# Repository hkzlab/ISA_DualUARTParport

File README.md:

# Dual UART + Parallel port ISA adapter

## Introduction

This board adds a parallel port and two serial (RS232) ports to computers with a free ISA slot.

The schematics of this board is heavily inspired by the parallel port schematics found in the IBM 5150 Technical Reference, with just a few
changes (IRQ level triggering and configurable port directionality) and by Sergey's floppy/serial controller.

Both serial ports and the parallel port addressing/IRQs are configurable.

### Disclaimer

I take NO responsibility for what happens if you decide to build and use this card. Your computer might crash, catch fire or be destroyed in other nasty ways.
Also, as this card is mostly based on the work of others, You're encourauged to take what you deem fit from this, and use it in your projects!

## Configuration

### Parallel port

#### Addressing

- 0x278: Leave JP1 open
- 0x378: Close JP1

#### IRQ

Parallel port interrupt number can be selected by placing a single vertical jumper on the **ParPort IRQ** block.

For example, a jumper placed on the last column of that block, will set the IRQ for the parallel port to number 7.

#### Directionality

The parallel port can be configured as an old style 4bit, monodirectional, parallel port by jumpering pins 2-3 of JP2.
PS/2 style bidirectional port can be configured by jumpering pins 1-2.

### Serial ports

IRQ and addressing of serial ports can be configured by properly jumpering the 3x8 jumper block at the center of the board.

IRQ selection is performed by the first 4 rows of the block: placing an horizontal jumper between columns 1-2 will select IRQ for the first serial port, between columns 2-3 will select
the IRQ for the second serial port.

The same principle applies for the IO address, selected by the last 4 rows of the block: jumpers between column 1-2 will select an address for port 1, and between column 2-3 for port 2.

#### Example

To select IO at 0x3F8 and IRQ4 for port 1, connect a jumper on 2nd row, first two columns, and another jumper on 8th row, column 1-2

## Bill of Materials

All ICs are in DIP package.

- 4x ~2.2k 1/4W resistors (**optional**, R1-R4). **These resistors will be on the TTL RX/TX lines**. To avoid loading them too much, use high-brightness leds and the highest resistor value you can use that still gives enough brightness!
- 4x 3mm LEDs (2x for UART RX indicators, 2x for TX) (**optional**)
- 1x 1.8432Mhz oscillator. DIP14 or DIP8
- 1x 8x4.7k bussed resistor array (9 pin)
- 1x 10x1.5k bussed resistor array (11 pin) (**optional**)
- 1x 10x LED bar, DIP20 (**optional**, socket this!)
- 8x 2.2nF / 25V ceramic capacitors, 5mm pitch
- 18x 100nF / 50v ceramic capacitors, 5mm pitch
- 4x 10uF / 50v electrolytic caps
- 2x 16C550 UARTs (16C450/16C650/16C750 should work, but are untested) in DIP40 format
- 2x 74HCT/LS138
- 2x 75C185
- 1x 74LS245
- 1x 74LS240
- 1x 74LS374
- 1x 74LS244
- 1x 74LS02
- 1x 74LS155
- 1x 74LS05
- 1x 74LS174
- 1x 74LS30
- 1x 74LS125
- 1x 74LS86
- 1x 2x13 pin header, 2.54mm
- 1x 2x4 pin header, 2.54mm
- 1x 2x8 pin header, 2.54mm
- 1x 1x8 pin header, 2.54mm
- 1x 1x2 pin header, 2.54mm
- 1x 1x3 pin header, 2.54mm
- 1x DB9 male, right angle, PCB mount (http://www.mouser.com/search/refine.aspx?Keyword=806-K22X-E9P-NJ15-99)
- 1x ISA card bracket - Keystone 9200-1 (http://www.mouser.com/ProductDetail/Keystone-Electronics/9200-1/?qs=sGAEpiMZZMsQtlBhqKq43VLJ3wppkop5) 

## Building notes

I **strongly advise AGAINST** soldering the LED bar for the parallel port: **socket it!** It is useful for debugging or to get some blinkenlights, but it loads the data pins, and some devices connected to the port might not like it. Socketing it will allow for a quick removal in case it becomes necessary.

RN2 depends on how bright you wish the LED bar to be, and how much load you want to put on the parallel port data pins. I usually fit an 1.5k resistor array.

## Credits

Thanks to [Sergey](http://www.malinov.com/Home/sergeys-projects) for all his projects!

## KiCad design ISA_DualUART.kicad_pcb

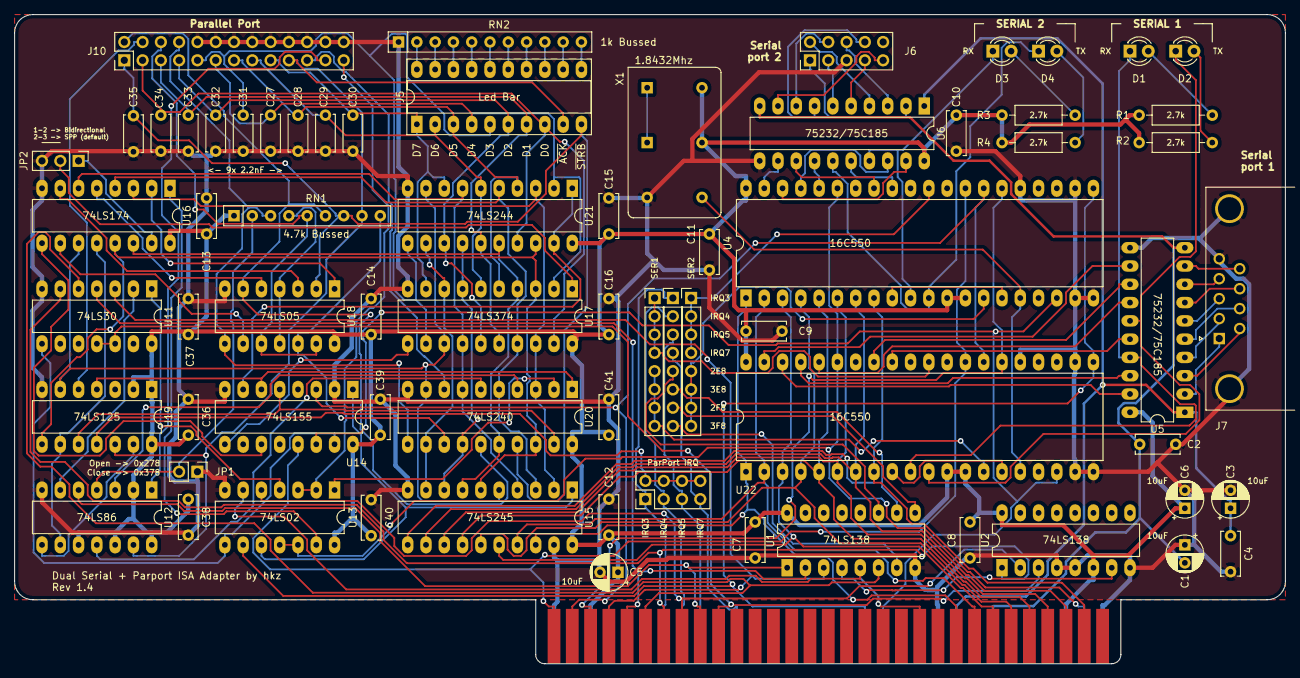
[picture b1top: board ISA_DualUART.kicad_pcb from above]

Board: 2 copper layers, 176.5 x 90.2 mm, 70 parts (0 on the bottom side), 138 nets.

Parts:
C1, C3, C5, C6: 10uF; CP_Radial_D5.0mm_P2.50mm
C2, C4, C7, C8, C9, C10, C11, C12, C13, C14, C15, C16, C36, C37, C38, C39, C40, C41: 100nF; C_Disc_D6.0mm_W2.5mm_P5.00mm
C27, C28, C29, C30, C31, C32, C33, C34, C35: 2.2nF; C_Disc_D5.0mm_W2.5mm_P5.00mm
D1: LED RX1; LED_D3.0mm
D2: LED TX1; LED_D3.0mm
D3: LED RX2; LED_D3.0mm
D4: LED TX2; LED_D3.0mm
J1: ISA BUS; Conn_Edge_PCB_ISA8
J2: ADDR_IRQ; PinHeader_1x08_P2.54mm_Vertical
J3: UART1_SEL; PinHeader_1x08_P2.54mm_Vertical
J4: UART2_SEL; PinHeader_1x08_P2.54mm_Vertical
J5: Parallel Port LEDs; DIP-20_W7.62mm_Socket_LongPads
J6: Serial 2 IDC; PinHeader_2x05_P2.54mm_Vertical
J7: Serial 1 DB9; DSUB-9_Male_Horizontal_P2.77x2.84mm_EdgePinOffset7.70mm_Hou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
J9: Parport IRQ Select; PinHeader_2x04_P2.54mm_Vertical
J10: Parallel Port; PinHeader_2x13_P2.54mm_Vertical
JP1: Address selection; PinHeader_1x02_P2.54mm_Vertical
JP2: Parport type; PinHeader_1x03_P2.54mm_Vertical
R1, R2, R3, R4: 2.7k; R_Axial_DIN0207_L6.3mm_D2.5mm_P10.16mm_Horizontal
RN1: 4.7k; R_Array_SIP9
RN2: 1k; R_Array_SIP11
U1, U2: 74LS138; DIP-16_W7.62mm_LongPads
U4, U22: 16550; DIP-40_W15.24mm_LongPads
U5, U6: GD75232N; DIP-20_W7.62mm_LongPads
U11: 74LS30; DIP-14_W7.62mm_LongPads
U12: 74LS86; DIP-14_W7.62mm_LongPads
U13: 74LS02; DIP-14_W7.62mm_LongPads
U14: 74LS155; DIP-16_W7.62mm_LongPads
U15: 74LS245; DIP-20_W7.62mm_LongPads
U16: 74LS174; DIP-16_W7.62mm_LongPads
U17: 74LS374; DIP-20_W7.62mm_LongPads
U18: 74LS05; DIP-14_W7.62mm_LongPads
U19: 74LS125; DIP-14_W7.62mm_LongPads
U20: 74LS240; DIP-20_W7.62mm_LongPads
U21: 74LS244; DIP-20_W7.62mm_LongPads
X1: 1.8432Mhz; Oscillator_DIP-14-8

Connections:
+12V: C3.1, C4.1, J1.9, U5.1, U6.1
-12V: C1.2, C2.2, J1.7, U5.10, U6.10
/0x2E8: J2.5, U1.11
/0x2F8: J2.7, U1.9
/0x3E8: J2.6, U1.10
/0x3F8: J2.8, U1.7
/A0: J1.62, U4.28, U14.13, U22.28
/A1: J1.61, U4.27, U14.3, U22.27
/A2: J1.60, U4.26, U22.26
/A3: J1.59, U1.3, U11.3
/A4: J1.58, U1.2, U11.4
/A5: J1.57, U1.6, U11.5
/A6: J1.56, U2.1, U11.6
/A7: J1.55, U2.2, U13.5
/A8: J1.54, U1.1, U12.5
/A9: J1.53, U2.3, U11.11, U11.12
/AEN: J1.42, U1.5, U13.6
/D0: J1.40, U4.1, U15.18, U22.1
/D1: J1.39, U4.2, U15.17, U22.2
/D2: J1.38, U4.3, U15.16, U22.3
/D3: J1.37, U4.4, U15.15, U22.4
/D4: J1.36, U4.5, U15.14, U22.5
/D5: J1.35, U4.6, U15.13, U22.6
/D6: J1.34, U4.7, U15.12, U22.7
/D7: J1.33, U4.8, U15.11, U22.8
/IRQ3: J1.25, J2.1, J9.1
/IRQ4: J1.24, J2.2, J9.3
/IRQ5: J1.23, J2.3, J9.5
/IRQ7: J1.21, J2.4, J9.7
/PARPORT_BD0: U15.2, U16.3, U17.18, U20.3, U21.3
/PARPORT_BD1: U15.3, U16.4, U17.17, U20.5, U21.5
/PARPORT_BD2: U15.4, U16.6, U17.14, U20.7, U21.7
/PARPORT_BD3: U15.5, U16.11, U17.13, U19.6, U20.9, U21.9
/PARPORT_BD4: U15.6, U16.13, U17.3, U19.8, U20.18, U21.18
/PARPORT_BD5: U15.7, U16.14, U17.4, U20.16, U21.16
/PARPORT_BD6: U15.8, U17.7, U20.14, U21.14
/PARPORT_BD7: U15.9, U17.8, U20.12, U21.12
/PARPORT_BUSY: J10.21, U20.8
/PARPORT_DATA0: C34.1, J5.8, J10.3, U17.19, U21.17
/PARPORT_DATA1: C33.1, J5.7, J10.5, U17.16, U21.15
/PARPORT_DATA2: C32.1, J5.6, J10.7, U17.15, U21.13
/PARPORT_DATA3: C31.1, J5.5, J10.9, U17.12, U21.11
/PARPORT_DATA4: C27.1, J5.4, J10.11, U17.2, U21.2
/PARPORT_DATA5: C28.1, J5.3, J10.13, U17.5, U21.4
/PARPORT_DATA6: C29.1, J5.2, J10.15, U17.6, U21.6
/PARPORT_DATA7: C30.1, J5.1, J10.17, U17.9, U21.8
/PARPORT_DIR: JP2.1, U16.15
/PARPORT_IRQ: U12.11, U20.6
/PARPORT_IRQEN: U12.9, U16.12, U19.9
/PARPORT_PE: J10.23, U12.1
/PARPORT_R: U13.10, U14.1, U15.1
/PARPORT_RPA: U14.7, U21.1, U21.19
/PARPORT_RPB: U14.6, U19.4, U20.1
/PARPORT_RPC: U14.5, U19.10, U20.19
/PARPORT_SLCT: J10.25, U13.2, U13.3
/PARPORT_WPA: U14.9, U17.11
/PARPORT_WPC: U14.11, U16.9
/RESETDRV: J1.2, U4.35, U13.11, U13.12, U22.35
/RN_1: JP1.2, RN1.2, U12.4
/RN_2: J10.8, RN1.3, U18.8, U20.11
/RN_3: RN1.4, U18.4, U18.11
/RN_4: J10.6, RN1.5, U18.10, U18.13
/RN_5: J10.2, RN1.6, U18.6, U20.15
/RN_6: C35.2, J5.10, J10.1, RN1.7, U18.2, U20.17
/RN_7: J5.9, J10.19, RN1.8, U12.13, U19.12
/RN_8: RN1.9, U18.12, U20.13
/RS232_1_CTS: J7.8, U5.7
/RS232_1_DCD: J7.1, U5.2
/RS232_1_DSR: J7.6, U5.3
/RS232_1_DTR: J7.4, U5.8
/RS232_1_RI: J7.9, U5.9
/RS232_1_RTS: J7.7, U5.5
/RS232_1_RX: J7.2, U5.4
/RS232_1_TX: J7.3, U5.6
/RS232_2_CTS: J6.8, U6.7
/RS232_2_DCD: J6.1, U6.2
/RS232_2_DSR: J6.6, U6.3
/RS232_2_DTR: J6.4, U6.8
/RS232_2_RI: J6.9, U6.9
/RS232_2_RTS: J6.7, U6.5
/RS232_2_RX: J6.2, U6.4
/RS232_2_TX: J6.3, U6.6
/SER_CLK: U4.16, U22.16, X1.8
/SIN_1: D1.1, U5.17, U22.10
/SIN_2: D3.1, U4.10, U6.17
/SOUT_1: D2.1, U5.15, U22.11
/SOUT_2: D4.1, U4.11, U6.15
/UART1_IRQ: J3.1, J3.2, J3.3, J3.4, U22.30
/UART2_IRQ: J4.1, J4.2, J4.3, J4.4, U4.30
/~CTS_1: U5.14, U22.36
/~CTS_2: U4.36, U6.14
/~DCD_1: U5.19, U22.38
/~DCD_2: U4.38, U6.19
/~DSR_1: U5.18, U22.37
/~DSR_2: U4.37, U6.18
/~DTR_1: U5.13, U22.33
/~DTR_2: U4.33, U6.13
/~IOR: J1.14, U4.21, U13.9, U22.21
/~IOW: J1.13, U4.18, U14.14, U22.18
/~PARPORT_ERROR: J10.4, U19.5
/~PARPORT_IRQEN: U12.8, U19.13
/~PARPORT_RESET: U13.13, U16.1
/~RI_1: U5.12, U22.39
/~RI_2: U4.39, U6.12
/~RTS_1: U5.16, U22.32
/~RTS_2: U4.32, U6.16
/~UART1_CS: J3.5, J3.6, J3.7, J3.8, U22.14
/~UART2_CS: J4.5, J4.6, J4.7, J4.8, U4.14
GND: C1.1, C2.1, C3.2, C4.2, C5.2, C6.2, C7.2, C8.2, C9.2, C10.2, C11.2, C12.1, C13.2, C14.2, C15.2, C16.2, C27.2, C28.2, C29.2, C30.2, C31.2, C32.2, C33.2, C34.2, C35.1, C36.2, C37.2, C38.2, C39.2, C40.2, C41.2, J1.1, J1.10, J1.31, J6.5, J7.0, J7.5, J10.10, J10.12, J10.14, J10.16, J10.18, J10.20, J10.22, J10.24, J10.26, JP1.1, JP2.3, RN2.1, U1.8, U2.4, U2.5, U2.8, U4.19, U4.20, U4.22, U4.25, U5.11, U6.11, U11.7, U12.7, U13.7, U14.2, U14.8, U15.10, U15.19, U16.8, U17.10, U18.7, U19.7, U20.10, U21.10, U22.19, U22.20, U22.22, U22.25, X1.7
unnamed: D1.2, R1.1
unnamed: D2.2, R2.1
unnamed: D3.2, R3.1
unnamed: D4.2, R4.1
unnamed: J5.11, RN2.11
unnamed: J5.12, RN2.10
unnamed: J5.13, RN2.9
unnamed: J5.14, RN2.8
unnamed: J5.15, RN2.7
unnamed: J5.16, RN2.6
unnamed: J5.17, RN2.5
unnamed: J5.18, RN2.4
unnamed: J5.19, RN2.3
unnamed: J5.20, RN2.2
unnamed: J9.2, J9.4, J9.6, J9.8, U19.11
unnamed: JP2.2, U17.1
unnamed: U1.4, U2.7
unnamed: U4.9, U4.15
unnamed: U11.1, U13.4
unnamed: U11.2, U12.6
unnamed: U11.8, U13.8, U14.15
unnamed: U12.3, U20.4
unnamed: U13.1, U20.2
unnamed: U16.2, U18.1
unnamed: U16.5, U18.5
unnamed: U16.7, U18.3
unnamed: U16.10, U18.9
unnamed: U22.9, U22.15
VCC: C5.1, C6.1, C7.1, C8.1, C9.1, C10.1, C11.1, C12.2, C13.1, C14.1, C15.1, C16.1, C36.1, C37.1, C38.1, C39.1, C40.1, C41.1, J1.3, J1.29, R1.2, R2.2, R3.2, R4.2, RN1.1, U1.16, U2.6, U2.16, U4.12, U4.13, U4.40, U5.20, U6.20, U11.14, U12.2, U12.10, U12.12, U12.14, U13.14, U14.16, U15.20, U16.16, U17.20, U18.14, U19.1, U19.2, U19.14, U20.20, U21.20, U22.12, U22.13, U22.40, X1.14

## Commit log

2021-01-17 Add submodules
2021-01-17 Add footprints and components
2021-01-17 Add custom module and new oscillator footprint
2021-01-17 Begin adding components
2021-01-17 Added all the required ICs
2021-01-17 Begin wiring UARTs
2021-01-17 First revision of the schematic
2021-01-18 Add gameport circuit
2021-01-18 Add gameport components
2021-01-19 Add more components of the parallel port
2021-01-19 More components of the parallel port
2021-01-19 First version of schematic for multifunction isa board
2021-01-21 Fix RPB line
2021-01-25 Begin organizing the board
2021-01-29 First model of the board
2021-01-29 Move some silk
2021-01-29 Moved around some components
2021-01-29 Move some components
2021-01-29 Chane connector
2021-01-29 Update PCB
2021-01-30 Add text and generate gerbers
2021-02-05 Change socket footprint to normal DIP
2021-02-05 Fix silkscreen
2021-02-05 Rerouted, now serial connector has shield to gnd
2021-02-06 Slightly better silkscreen
2021-02-08 Rewire parallel port connector
2021-02-08 Rerouted card
2021-02-08 Changed organization of parport connector
2021-02-09 Invert IRQ sensing to conform to AT specs
2021-02-10 Reworked the board, added LED indicators for parport
2021-02-10 Fixed silkscreen
2021-02-10 Another silkscreen fix
2021-02-10 Rotate parport and serial headers
2021-02-10 Updated schematics
2021-02-11 Forgot gerbers for rev 1.1
2021-02-11 Update silkscreen
2021-02-14 Add modification notes
2021-02-23 Update solder mask
2021-03-10 Minor silkscreen fix
2021-03-10 Other minor silkscreen fixes
2021-03-10 More silkscreen fixes
2021-03-10 Begin writing the README
2021-03-10 Add README
2021-03-10 Add BOM and resized pic
2021-03-10 Slight change to README
2021-03-10 Add other notes to readme
2021-03-10 Add missing caps from BOM
2021-03-10 Fix typo
2021-03-21 Slight changes to silkscreen
2021-03-21 Mark revision as 1.4
2021-11-09 Update kicad url
